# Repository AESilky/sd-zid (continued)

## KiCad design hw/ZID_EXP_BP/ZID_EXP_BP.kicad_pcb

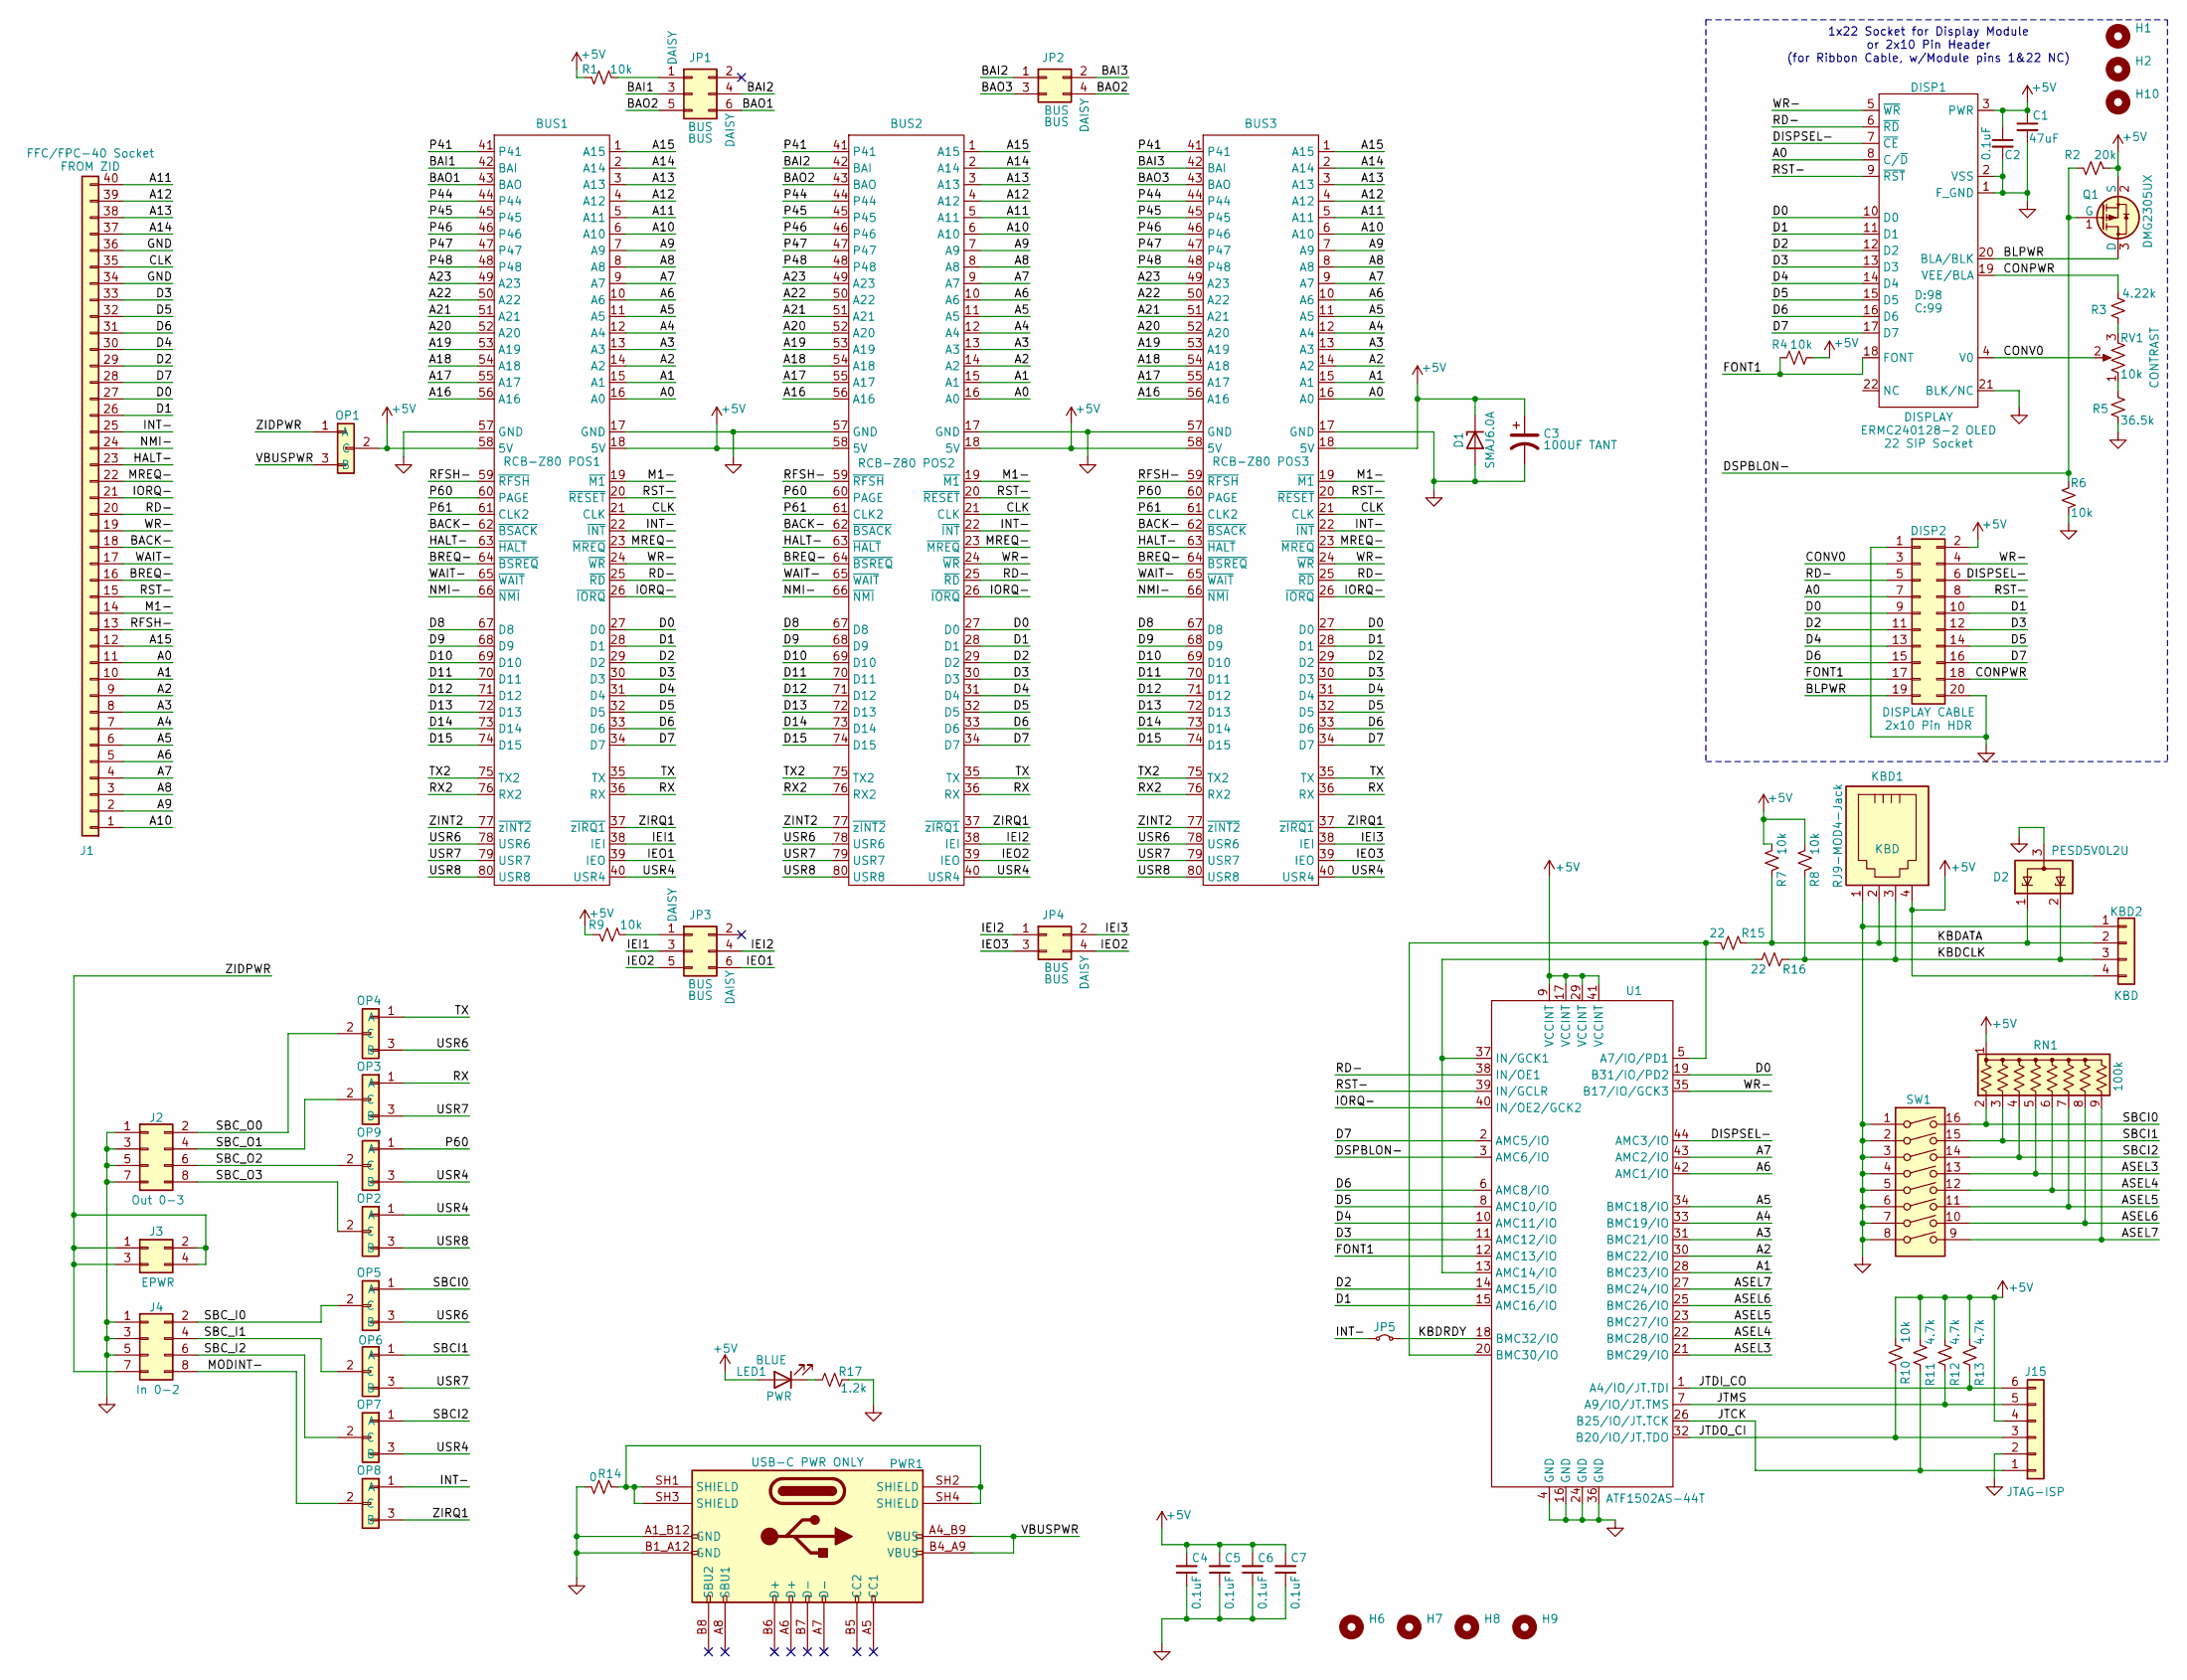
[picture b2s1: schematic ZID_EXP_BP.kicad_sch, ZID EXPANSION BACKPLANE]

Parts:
BUS1, BUS2, BUS3: RC80-BUS-BPMB-AES
C1: 47uF; C_1210_3225Metric_Pad1.33x2.70mm_HandSolder
C2, C4, C5, C6, C7: 0.1uF; C_0603_1608Metric
C3: 100UF TANT; CP_EIA-7343-31_Kemet-D_HandSolder
D1: SMAJ6.0A; D_SMA
D2: PESD5V0L2U; SOT-323_SC-70
DISP1: DISPLAY; PinSocket_1x22_P2.54mm_Vertical; PartOpt1 22 SIP Socket
DISP2: HDR 2x10 Pin; PinHeader_2x10_P2.54mm_Vertical; PartOpt1 2x10 Pin HDR
H1, H2, H6, H7, H8, H9, H10: MountingHole; MountingHole_3.2mm_M3
J1: FFC/FPC-40 Socket; CviLux_CF25401D0-05-NH_FFC-FPC-AES
J2, J4: Conn 2x04 0.1" pin; PinHeader_2x04_P2.54mm_Vertical
J3: Conn 2x02 0.1" pin; PinHeader_2x02_P2.54mm_Vertical
J15: JST-PH-K B6B; JST_PH_B6B-PH-K_1x06_P2.00mm_Vertical
JP1, JP3: Conn_02x03_Odd_Even; PinHeader_2x03_P2.54mm_Vertical
JP2, JP4: Conn 2x02 HDR Pin 2.54mm; PinHeader_2x02_P2.54mm_Vertical
JP5: Conn 1x02 HDR Pin 2.0mm; PinHeader_1x02_P2.00mm_Vertical
KBD1: RJ9-MOD4-Jack; FCI-68897-001LF-ModJack4-Horz-AES
KBD2: Conn 01x04 Pin hdr 0.1in; PinHeader_1x04_P2.54mm_Vertical
LED1: LED BLUE; LED_0805_2012Metric
OP1, OP2, OP3, OP4, OP5, OP6, OP7, OP8, OP9: AES-Option_A-B; PinHeader_1x03_P2.54mm_Vertical
PWR1: USB-C PWR ONLY; AES-USB_C-Molex-BdTopMnt-2171790001
Q1: DMG2305UX; DMG2305-SOT-23-3-AES
R1, R4, R6, R7, R8, R9, R10: 10k; R_0805_2012Metric
R2: 20k; R_0805_2012Metric
R3: 4.22k; R_0805_2012Metric
R5: 36.5k; R_0805_2012Metric
R11, R12, R13: 4.7k; R_0805_2012Metric
R14: 0; R_0805_2012Metric
R15, R16: 22; R_0805_2012Metric
R17: 1.2k; R_0805_2012Metric
RN1: 100k; R_Array_SIP9
RV1: 10k; Pot-Molence-Amazon-PCB-AES
SW1: SW_DIP_x08; DIP-16_W7.62mm_LongPads
U1: ATF1502AS-44T; TQFP-44_10x10mm_P0.8mm

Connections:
+5V: BUS1.18 (5V), BUS1.58 (5V), BUS2.18 (5V), BUS2.58 (5V), BUS3.18 (5V), BUS3.58 (5V), C1.1, C2.1, C3.1, C4.2, C5.2, C6.2, C7.2, D1.1 (K), DISP1.3 (PWR), DISP2.2, J15.4, KBD1.4, KBD2.4, LED1.2 (A), OP1.2 (C), Q1.2 (S), R1.1, R2.1, R4.2, R7.2, R8.2, R9.1, R10.1, R11.1, R12.1, R13.1, RN1.1 (common), U1.9 (VCCINT), U1.17 (VCCINT), U1.29 (VCCINT), U1.41 (VCCINT)
/A0: BUS1.16 (A0), BUS2.16 (A0), BUS3.16 (A0), DISP1.8 (C/~D), DISP2.7, J1.11
/A1: BUS1.15 (A1), BUS2.15 (A1), BUS3.15 (A1), J1.10, U1.28 (BMC23/IO)
/A2: BUS1.14 (A2), BUS2.14 (A2), BUS3.14 (A2), J1.9, U1.30 (BMC22/IO)
/A3: BUS1.13 (A3), BUS2.13 (A3), BUS3.13 (A3), J1.8, U1.31 (BMC21/IO)
/A4: BUS1.12 (A4), BUS2.12 (A4), BUS3.12 (A4), J1.7, U1.33 (BMC19/IO)
/A5: BUS1.11 (A5), BUS2.11 (A5), BUS3.11 (A5), J1.6, U1.34 (BMC18/IO)
/A6: BUS1.10 (A6), BUS2.10 (A6), BUS3.10 (A6), J1.5, U1.42 (AMC1/IO)
/A7: BUS1.9 (A7), BUS2.9 (A7), BUS3.9 (A7), J1.4, U1.43 (AMC2/IO)
/A8: BUS1.8 (A8), BUS2.8 (A8), BUS3.8 (A8), J1.3
/A9: BUS1.7 (A9), BUS2.7 (A9), BUS3.7 (A9), J1.2
/A10: BUS1.6 (A10), BUS2.6 (A10), BUS3.6 (A10), J1.1
/A11: BUS1.5 (A11), BUS2.5 (A11), BUS3.5 (A11), J1.40
/A12: BUS1.4 (A12), BUS2.4 (A12), BUS3.4 (A12), J1.39
/A13: BUS1.3 (A13), BUS2.3 (A13), BUS3.3 (A13), J1.38
/A14: BUS1.2 (A14), BUS2.2 (A14), BUS3.2 (A14), J1.37
/A15: BUS1.1 (A15), BUS2.1 (A15), BUS3.1 (A15), J1.12
/A16: BUS1.56 (A16), BUS2.56 (A16), BUS3.56 (A16)
/A17: BUS1.55 (A17), BUS2.55 (A17), BUS3.55 (A17)
/A18: BUS1.54 (A18), BUS2.54 (A18), BUS3.54 (A18)
/A19: BUS1.53 (A19), BUS2.53 (A19), BUS3.53 (A19)
/A20: BUS1.52 (A20), BUS2.52 (A20), BUS3.52 (A20)
/A21: BUS1.51 (A21), BUS2.51 (A21), BUS3.51 (A21)
/A22: BUS1.50 (A22), BUS2.50 (A22), BUS3.50 (A22)
/A23: BUS1.49 (A23), BUS2.49 (A23), BUS3.49 (A23)
/ASEL3: RN1.5 (R4), SW1.13, U1.21 (BMC29/IO)
/ASEL4: RN1.6 (R5), SW1.12, U1.22 (BMC28/IO)
/ASEL5: RN1.7 (R6), SW1.11, U1.23 (BMC27/IO)
/ASEL6: RN1.8 (R7), SW1.10, U1.25 (BMC26/IO)
/ASEL7: RN1.9 (R8), SW1.9, U1.27 (BMC24/IO)
/BACK-: BUS1.62 (~BSACK), BUS2.62 (~BSACK), BUS3.62 (~BSACK), J1.18
/BAI1: BUS1.42 (BAI), JP1.3
/BAI2: BUS2.42 (BAI), JP1.4, JP2.1
/BAI3: BUS3.42 (BAI), JP2.2
/BAO1: BUS1.43 (BAO), JP1.6
/BAO2: BUS2.43 (BAO), JP1.5, JP2.4
/BAO3: BUS3.43 (BAO), JP2.3
/BLPWR: DISP1.20 (BLA/BLK), DISP2.19, Q1.3 (D)
/BREQ-: BUS1.64 (~BSREQ), BUS2.64 (~BSREQ), BUS3.64 (~BSREQ), J1.16
/CLK: BUS1.21 (CLK), BUS2.21 (CLK), BUS3.21 (CLK), J1.35
/CONPWR: DISP1.19 (VEE/BLA), DISP2.18, R3.1
/CONV0: DISP1.4 (V0), DISP2.3, RV1.2
/D0: BUS1.27 (D0), BUS2.27 (D0), BUS3.27 (D0), DISP1.10 (D0), DISP2.9, J1.27, U1.19 (B31/IO/PD2)
/D1: BUS1.28 (D1), BUS2.28 (D1), BUS3.28 (D1), DISP1.11 (D1), DISP2.10, J1.26, U1.15 (AMC16/IO)
/D2: BUS1.29 (D2), BUS2.29 (D2), BUS3.29 (D2), DISP1.12 (D2), DISP2.11, J1.29, U1.14 (AMC15/IO)
/D3: BUS1.30 (D3), BUS2.30 (D3), BUS3.30 (D3), DISP1.13 (D3), DISP2.12, J1.33, U1.11 (AMC12/IO)
/D4: BUS1.31 (D4), BUS2.31 (D4), BUS3.31 (D4), DISP1.14 (D4), DISP2.13, J1.30, U1.10 (AMC11/IO)
/D5: BUS1.32 (D5), BUS2.32 (D5), BUS3.32 (D5), DISP1.15 (D5), DISP2.14, J1.32, U1.8 (AMC10/IO)
/D6: BUS1.33 (D6), BUS2.33 (D6), BUS3.33 (D6), DISP1.16 (D6), DISP2.15, J1.31, U1.6 (AMC8/IO)
/D7: BUS1.34 (D7), BUS2.34 (D7), BUS3.34 (D7), DISP1.17 (D7), DISP2.16, J1.28, U1.2 (AMC5/IO)
/D8: BUS1.67 (D8), BUS2.67 (D8), BUS3.67 (D8)
/D9: BUS1.68 (D9), BUS2.68 (D9), BUS3.68 (D9)
/D10: BUS1.69 (D10), BUS2.69 (D10), BUS3.69 (D10)
/D11: BUS1.70 (D11), BUS2.70 (D11), BUS3.70 (D11)
/D12: BUS1.71 (D12), BUS2.71 (D12), BUS3.71 (D12)
/D13: BUS1.72 (D13), BUS2.72 (D13), BUS3.72 (D13)
/D14: BUS1.73 (D14), BUS2.73 (D14), BUS3.73 (D14)
/D15: BUS1.74 (D15), BUS2.74 (D15), BUS3.74 (D15)
/DISPSEL-: DISP1.7 (~CE), DISP2.6, U1.44 (AMC3/IO)
/DSPBLON-: Q1.1 (G), R2.2, R6.1, U1.3 (AMC6/IO)
/FONT1: DISP1.18 (FONT), DISP2.17, R4.1, U1.12 (AMC13/IO)
/HALT-: BUS1.63 (~HALT), BUS2.63 (~HALT), BUS3.63 (~HALT), J1.23
/IEI1: BUS1.38 (IEI), JP3.3
/IEI2: BUS2.38 (IEI), JP3.4, JP4.1
/IEI3: BUS3.38 (IEI), JP4.2
/IEO1: BUS1.39 (IEO), JP3.6
/IEO2: BUS2.39 (IEO), JP3.5, JP4.4
/IEO3: BUS3.39 (IEO), JP4.3
/INT-: BUS1.22 (~INT), BUS2.22 (~INT), BUS3.22 (~INT), J1.25, JP5.2 (B), OP8.1 (A)
/IORQ-: BUS1.26 (~IORQ), BUS2.26 (~IORQ), BUS3.26 (~IORQ), J1.21, U1.40 (IN/OE2/GCK2)
/JTCK: J15.1, R11.2, U1.26 (B25/IO/JT.TCK)
/JTDI_CO: J15.6, R13.2, U1.1 (A4/IO/JT.TDI)
/JTDO_CI: J15.3, R10.2, U1.32 (B20/IO/JT.TDO)
/JTMS: J15.5, R12.2, U1.7 (A9/IO/JT.TMS)
/KBDATA: D2.1 (K), KBD1.2, KBD2.2, R7.1, R15.1
/KBDCLK: D2.2 (K), KBD1.3, KBD2.3, R8.1, R16.1
/KBDRDY: JP5.1 (A), U1.18 (BMC32/IO)
/M1-: BUS1.19 (~M1), BUS2.19 (~M1), BUS3.19 (~M1), J1.14
/MODINT-: J4.8, OP8.2 (C)
/MREQ-: BUS1.23 (~MREQ), BUS2.23 (~MREQ), BUS3.23 (~MREQ), J1.22
/NMI-: BUS1.66 (~NMI), BUS2.66 (~NMI), BUS3.66 (~NMI), J1.24
/P41: BUS1.41, BUS2.41, BUS3.41
/P44: BUS1.44, BUS2.44, BUS3.44
/P45: BUS1.45, BUS2.45, BUS3.45
/P46: BUS1.46, BUS2.46, BUS3.46
/P47: BUS1.47, BUS2.47, BUS3.47
/P48: BUS1.48, BUS2.48, BUS3.48
/P60: BUS1.60 (PAGE), BUS2.60 (PAGE), BUS3.60 (PAGE), OP9.1 (A)
/P61: BUS1.61 (CLK2), BUS2.61 (CLK2), BUS3.61 (CLK2)
/RD-: BUS1.25 (~RD), BUS2.25 (~RD), BUS3.25 (~RD), DISP1.6 (~RD), DISP2.5, J1.20, U1.38 (IN/OE1)
/RFSH-: BUS1.59 (~RFSH), BUS2.59 (~RFSH), BUS3.59 (~RFSH), J1.13
/RST-: BUS1.20 (~RESET), BUS2.20 (~RESET), BUS3.20 (~RESET), DISP1.9 (~RST), DISP2.8, J1.15, U1.39 (IN/GCLR)
/RX: BUS1.36 (RX), BUS2.36 (RX), BUS3.36 (RX), OP3.1 (A)
/RX2: BUS1.76 (RX2), BUS2.76 (RX2), BUS3.76 (RX2)
/SBCI0: OP5.1 (A), RN1.2 (R1), SW1.16
/SBCI1: OP6.1 (A), RN1.3 (R2), SW1.15
/SBCI2: OP7.1 (A), RN1.4 (R3), SW1.14
/SBC_I0: J4.2, OP5.2 (C)
/SBC_I1: J4.4, OP6.2 (C)
/SBC_I2: J4.6, OP7.2 (C)
/SBC_O0: J2.2, OP4.2 (C)
/SBC_O1: J2.4, OP3.2 (C)
/SBC_O2: J2.6, OP9.2 (C)
/SBC_O3: J2.8, OP2.2 (C)
/TX: BUS1.35 (TX), BUS2.35 (TX), BUS3.35 (TX), OP4.1 (A)
/TX2: BUS1.75 (TX2), BUS2.75 (TX2), BUS3.75 (TX2)
/USR4: BUS1.40 (USR4), BUS2.40 (USR4), BUS3.40 (USR4), OP2.1 (A), OP7.3 (B), OP9.3 (B)
/USR6: BUS1.78 (USR6), BUS2.78 (USR6), BUS3.78 (USR6), OP4.3 (B), OP5.3 (B)
/USR7: BUS1.79 (USR7), BUS2.79 (USR7), BUS3.79 (USR7), OP3.3 (B), OP6.3 (B)
/USR8: BUS1.80 (USR8), BUS2.80 (USR8), BUS3.80 (USR8), OP2.3 (B)
/VBUSPWR: OP1.3 (B), PWR1.A4_B9 (VBUS), PWR1.B4_A9 (VBUS)
/WAIT-: BUS1.65 (~WAIT), BUS2.65 (~WAIT), BUS3.65 (~WAIT), J1.17
/WR-: BUS1.24 (~WR), BUS2.24 (~WR), BUS3.24 (~WR), DISP1.5 (~WR), DISP2.4, J1.19, U1.35 (B17/IO/GCK3)
/ZIDPWR: J3.1, J3.2, J3.3, J3.4, J4.7, OP1.1 (A)
/ZINT2: BUS1.77 (~zINT2), BUS2.77 (~zINT2), BUS3.77 (~zINT2)
/ZIRQ1: BUS1.37 (~zIRQ1), BUS2.37 (~zIRQ1), BUS3.37 (~zIRQ1), OP8.3 (B)
GND: BUS1.17 (GND), BUS1.57 (GND), BUS2.17 (GND), BUS2.57 (GND), BUS3.17 (GND), BUS3.57 (GND), C1.2, C2.2, C3.2, C4.1, C5.1, C6.1, C7.1, D1.2 (A), D2.3 (A), DISP1.1 (F_GND), DISP1.2 (VSS), DISP1.21 (BLK/NC), DISP2.1, DISP2.20, J1.34, J1.36, J2.1, J2.3, J2.5, J2.7, J4.1, J4.3, J4.5, J15.2, KBD1.1, KBD2.1, PWR1.A1_B12 (GND), PWR1.B1_A12 (GND), R5.2, R6.2, R14.2, R17.2, SW1.1, SW1.2, SW1.3, SW1.4, SW1.5, SW1.6, SW1.7, SW1.8, U1.4 (GND), U1.16 (GND), U1.24 (GND), U1.36 (GND)
unnamed: JP1.1, R1.2
unnamed: JP3.1, R9.2
unnamed: LED1.1 (K), R17.1
unnamed: PWR1.SH1 (SHIELD), PWR1.SH2 (SHIELD), PWR1.SH3 (SHIELD), PWR1.SH4 (SHIELD), R14.1
unnamed: R3.2, RV1.3
unnamed: R5.1, RV1.1
unnamed: R15.2, U1.5 (A7/IO/PD1), U1.20 (BMC30/IO)
unnamed: R16.2, U1.13 (AMC14/IO), U1.37 (IN/GCK1)

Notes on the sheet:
1x22 Socket for Display Module or 2x10 Pin Header (for Ribbon Cable, w/Module pins 1&22 NC)

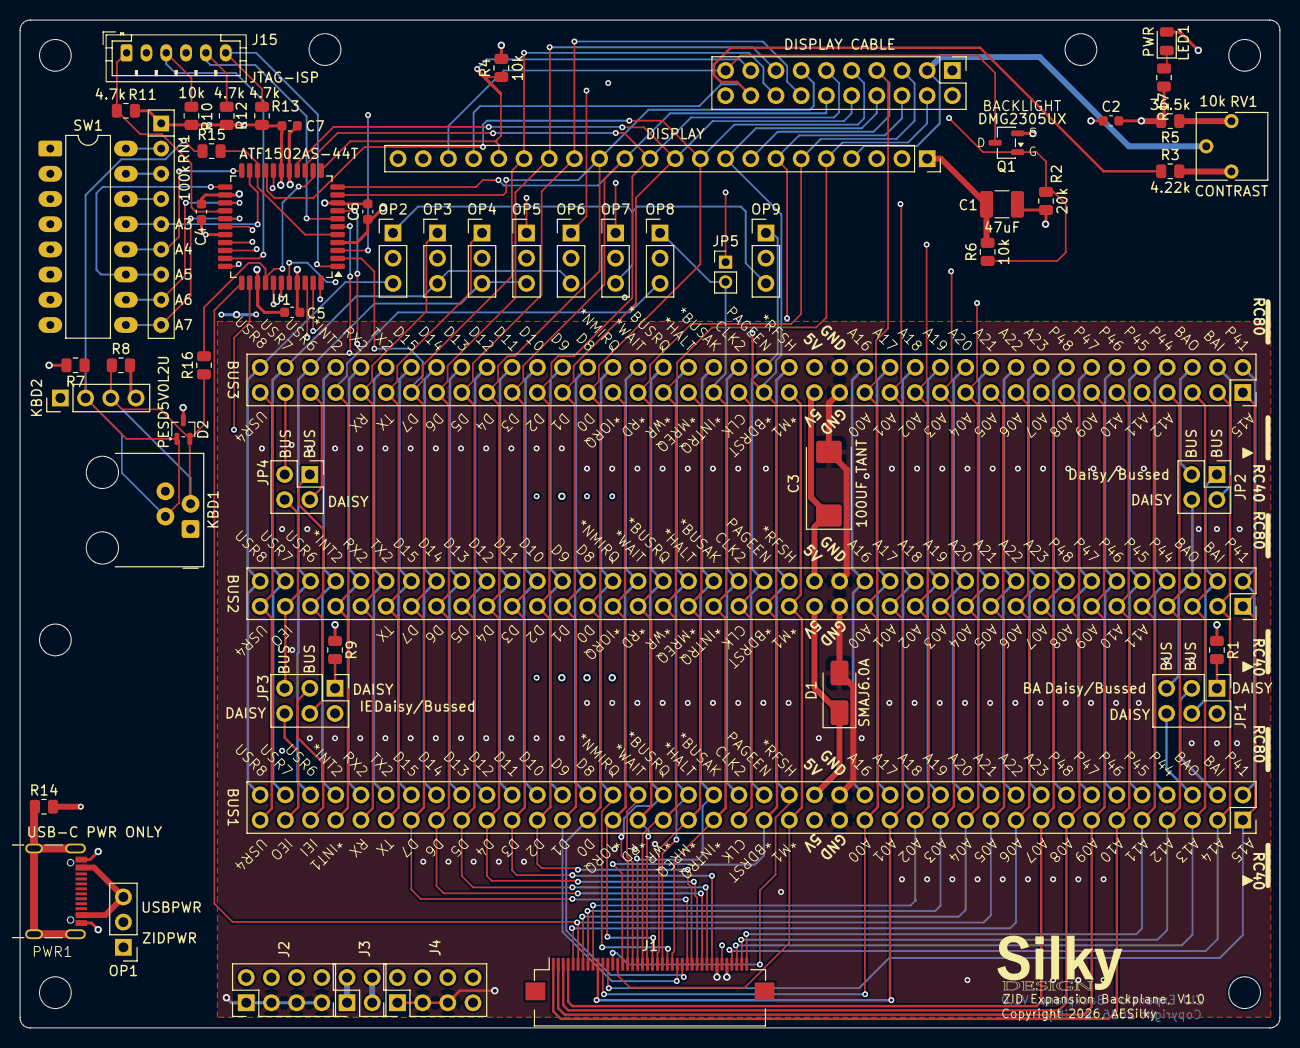
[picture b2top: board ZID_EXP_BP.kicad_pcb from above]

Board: 4 copper layers, 127.0 x 101.6 mm, 66 parts (0 on the bottom side), 125 nets.

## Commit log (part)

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2026-02-24 Initial
2026-02-24 Revise README for ZID Debug Board details
    Updated the README to reflect the new ZID Z80 In-circuit Debug Board features and functionality.
2026-02-24 Doc: add block diagram
2026-02-27 . significant zid_mail pld work
2026-02-28 . pld 1st cut complete
2026-03-05 CPLD: Early main logic
2026-03-16 CPLD testing #1
2026-03-27 CPLD: zsr, mmu, sbcgp, dbi working
2026-03-29 CPLD tested break and reset
2026-03-29 CPLD: Pins assigned
2026-03-31 SCHM: Initial
2026-04-01 SCHM: Initial ERC passed
2026-04-01 Only ignore PDF from PLD outputs
2026-04-03 Pin-keeper on control, addr, and data. Refresh gated MREQ for debug.
2026-04-03 Update dates. Archive small break compare PAL.
2026-04-04 Address pull-ups, small updates.
2026-04-05 Add TP for open CPLD pins
2026-04-05 8 output bits on RP. 10k PU for most. TVS.
2026-04-06 U24 from LVC to AHCT for 5V
2026-04-07 Footprints assigned
2026-04-07 Bypass caps
2026-04-07 74LVC3G04, free up BUSACK_H and BUSACK_L.
2026-04-08 Break exp conn 2x20
2026-04-09 PCB comp place #1
2026-04-10 PCB layout 2
2026-04-10 PCB-Main layout 3
2026-04-11 POD start PCB
2026-04-12 PCB Main: layout 20250411a
2026-04-12 POD-1 pcb
2026-04-13 POD PCB 4 layouts
2026-04-14 POD PCB increase GND trace width
2026-04-15 Exp-BP: Add display
2026-04-15 Schm plots
2026-04-16 BRK EXP initial schematic
2026-04-17 BP-EXP: 1 board only. PLCC-DIP: Adapter form.
2026-04-18 EXP-BP: Bypass caps, contrast R values
2026-04-18 Change ZID,POD,ExpBP connector to SIP
2026-04-19 Change bulk caps, J1 symbol
2026-04-20 Timing Diag: Debug to Target Mode
2026-04-20 ZID Main: TVS from SMC5.0 to SMA6.0
2026-04-20 Timing: BRK IF AD EQ
2026-04-21 74FCT541 to 74FCT2245. Move GND around CLK on ZID-POD connector
2026-04-24 Timing: IF worst-case (wip)
2026-04-24 Timing: 20MHz IF worst/best
2026-04-25 Timing: IF Memory RD
2026-04-26 Timing: Break MR wData worst-case
2026-04-27 Timing: Brk MR wData worst & best
2026-04-28 Timing: Break IF b/w MR-Data b/w
2026-04-30 Timing: Fix error in IF AEQ best
2026-04-30 PLD: Update logic to match diagrams.
2026-05-08 PLD: Minor logic changes. Trying to get mod_sel working.
2026-05-10 RPM Interface doc
2026-05-10 Test ROM with the region number in each region
2026-05-15 DBM: Initial (test) DB Monitor and SBC code
2026-05-20 PLD: Work around Microchip negative logic issue. PCB add external break.
2026-05-20 DM: Boot and SBC initial code.
2026-05-31 PLD: Replace LOW-TRUE pin terms with neg-logic
2026-05-31 DOC: CTRL/Data initial
2026-06-03 PLD: Negative logic (somewhat working), before switch to high-true ROM/RAM enable.
2026-06-03 CALC: Functional HP-16C'ish calculator.
2026-06-07 Z: RST8 Handling & SBC additional funcs. DOC: ADD & SUB commands and BIN nbase support.
2026-06-09 DM: Adjust RST8 code. DOC: Add debugging to PIO code.
2026-06-20 PLD: Positive ROM_SEL pin
2026-06-20 PLD: ROM_SEL HIGH-TRUE, RAM_SEL LOW-TRUE
2026-06-20 DC: LOAD/LD command. Work on bus interface.
2026-06-25 SCHM: Update CPLD pins and put all break units on board.
2026-06-25 RP-DC: LD,LOAD,DUMP,INC,DEC implemented.
2026-06-25 DM: DB Monitor basic working. Ram moved up.
2026-06-26 SCHM: Updates per SM
2026-06-29 DOC: Initial DM/DOC comm/cmds functional.
2026-06-29 DM: Initial DM/DOC comm/cmds functional.
2026-06-30 PLD: Keep ZID CTRL bits safe during Single-Step and Single Port Writes.
2026-06-30 HW: Ready to lay out.
2026-06-30 HW: Remove accedentally tracked 'fp-info-cache'
